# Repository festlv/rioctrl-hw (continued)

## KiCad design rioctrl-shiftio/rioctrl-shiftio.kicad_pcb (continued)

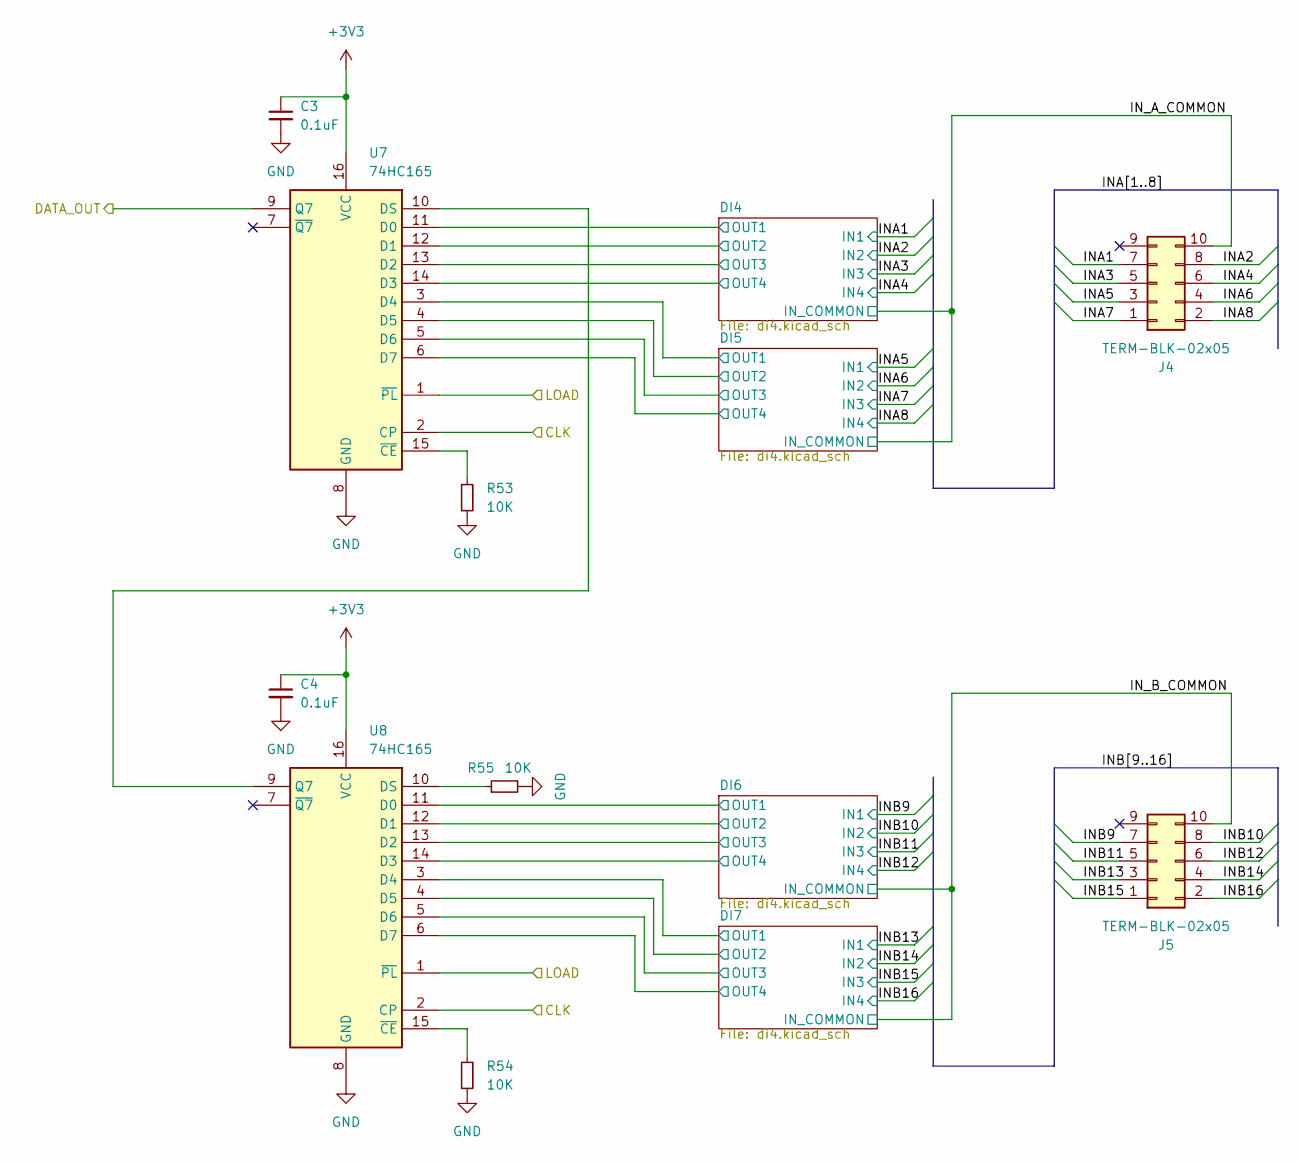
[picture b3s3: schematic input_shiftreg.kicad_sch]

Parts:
C3, C4: 0.1uF; C_0603_1608Metric; LCSC# C14663
J4, J5: TERM-BLK-02x05; JL15EDGRHC-35005B02; MPN JL15EDGRHC-35005B02; LCSC# C2908411
R53, R54, R55: 10K; R_0603_1608Metric; LCSC# C98220
U7, U8: 74HC165; SO-16_3.9x9.9mm_P1.27mm; MPN 74HC165D,653; LCSC# C5613

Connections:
+3V3: C3.1, C4.1, U7.16 (VCC), U8.16 (VCC); also elsewhere on the board
/Input shiftreg/CLK: U7.2 (CP), U8.2 (CP); also elsewhere on the board
/Input shiftreg/DATA_OUT: U7.9 (Q7); also elsewhere on the board
/Input shiftreg/DI4/OUT1: U7.11 (D0); also elsewhere on the board
/Input shiftreg/DI4/OUT2: U7.12 (D1); also elsewhere on the board
/Input shiftreg/DI4/OUT3: U7.13 (D2); also elsewhere on the board
/Input shiftreg/DI4/OUT4: U7.14 (D3); also elsewhere on the board
/Input shiftreg/DI5/OUT1: U7.3 (D4); also elsewhere on the board
/Input shiftreg/DI5/OUT2: U7.4 (D5); also elsewhere on the board
/Input shiftreg/DI5/OUT3: U7.5 (D6); also elsewhere on the board
/Input shiftreg/DI5/OUT4: U7.6 (D7); also elsewhere on the board
/Input shiftreg/DI6/OUT1: U8.11 (D0); also elsewhere on the board
/Input shiftreg/DI6/OUT2: U8.12 (D1); also elsewhere on the board
/Input shiftreg/DI6/OUT3: U8.13 (D2); also elsewhere on the board
/Input shiftreg/DI6/OUT4: U8.14 (D3); also elsewhere on the board
/Input shiftreg/DI7/OUT1: U8.3 (D4); also elsewhere on the board
/Input shiftreg/DI7/OUT2: U8.4 (D5); also elsewhere on the board
/Input shiftreg/DI7/OUT3: U8.5 (D6); also elsewhere on the board
/Input shiftreg/DI7/OUT4: U8.6 (D7); also elsewhere on the board
/Input shiftreg/INA1: J4.7; also elsewhere on the board
/Input shiftreg/INA2: J4.8; also elsewhere on the board
/Input shiftreg/INA3: J4.5; also elsewhere on the board
/Input shiftreg/INA4: J4.6; also elsewhere on the board
/Input shiftreg/INA5: J4.3; also elsewhere on the board
/Input shiftreg/INA6: J4.4; also elsewhere on the board
/Input shiftreg/INA7: J4.1; also elsewhere on the board
/Input shiftreg/INA8: J4.2; also elsewhere on the board
/Input shiftreg/INB9: J5.7; also elsewhere on the board
/Input shiftreg/INB10: J5.8; also elsewhere on the board
/Input shiftreg/INB11: J5.5; also elsewhere on the board
/Input shiftreg/INB12: J5.6; also elsewhere on the board
/Input shiftreg/INB13: J5.3; also elsewhere on the board
/Input shiftreg/INB14: J5.4; also elsewhere on the board
/Input shiftreg/INB15: J5.1; also elsewhere on the board
/Input shiftreg/INB16: J5.2; also elsewhere on the board
/Input shiftreg/IN_A_COMMON: J4.10; also elsewhere on the board
/Input shiftreg/IN_B_COMMON: J5.10; also elsewhere on the board
/Input shiftreg/LOAD: U7.1 (~PL), U8.1 (~PL); also elsewhere on the board
GND: C3.2, C4.2, R53.2, R54.2, R55.2, U7.8 (GND), U8.8 (GND); also elsewhere on the board
unnamed: U7.10 (DS), U8.9 (Q7)
unnamed: R53.1, U7.15 (~CE)
unnamed: R55.1, U8.10 (DS)
unnamed: R54.1, U8.15 (~CE)

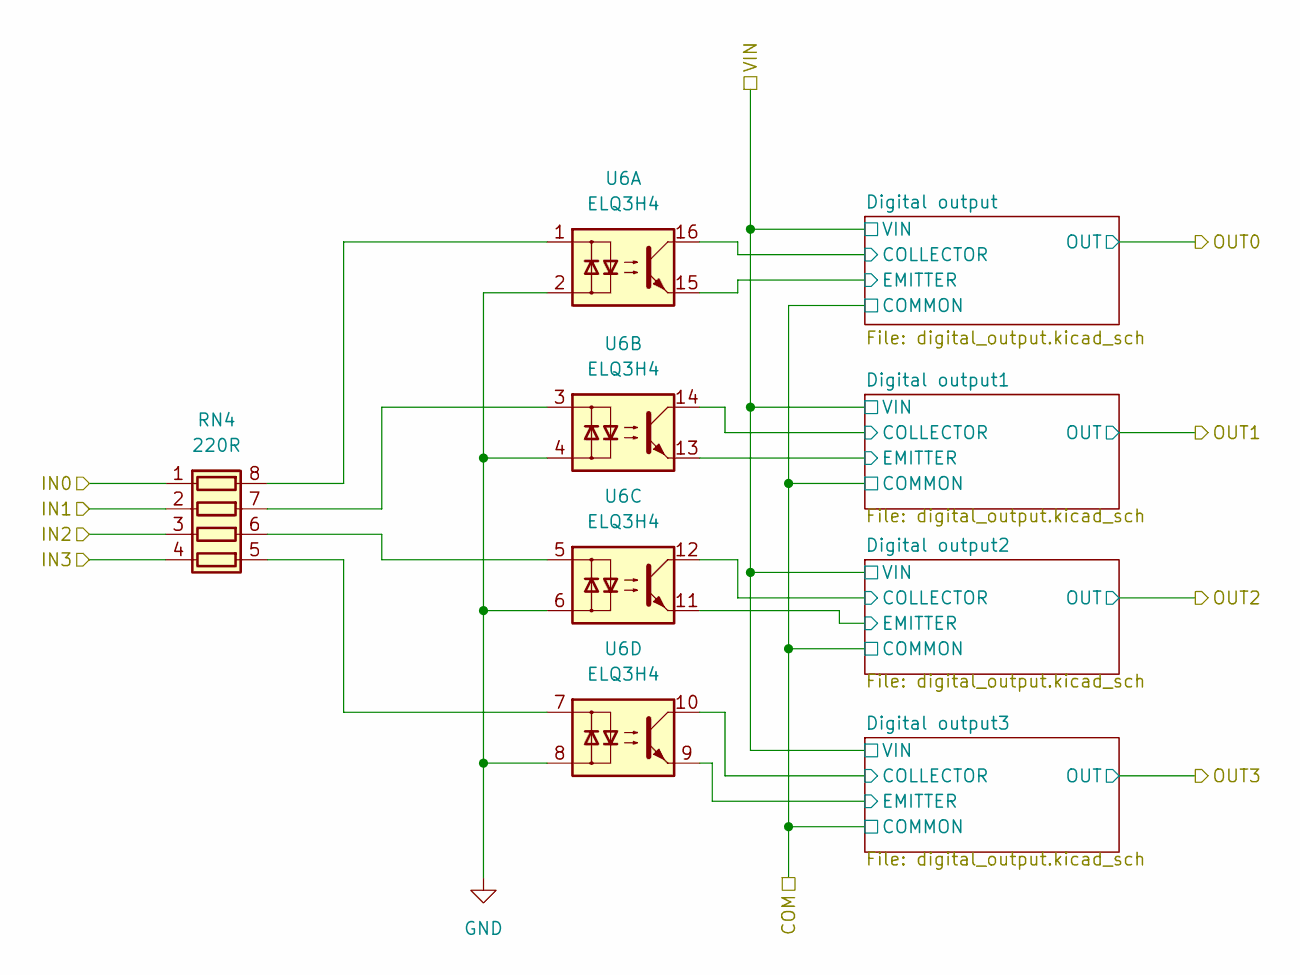
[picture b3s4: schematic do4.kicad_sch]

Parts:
RN4: 220R; R_Array_Convex_4x0603; LCSC# C706474
U6: ELQ3H4; SOIC-16W_5.3x10.2mm_P1.27mm; MPN ELQ3H4(TA)-G; LCSC# C150957

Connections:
/Output shiftreg/DOB2/Digital output1/COLLECTOR: U6.14; also elsewhere on the board
/Output shiftreg/DOB2/Digital output1/EMITTER: U6.13; also elsewhere on the board
/Output shiftreg/DOB2/Digital output2/COLLECTOR: U6.12; also elsewhere on the board
/Output shiftreg/DOB2/Digital output2/EMITTER: U6.11; also elsewhere on the board
/Output shiftreg/DOB2/Digital output3/COLLECTOR: U6.10; also elsewhere on the board
/Output shiftreg/DOB2/Digital output3/EMITTER: U6.9; also elsewhere on the board
/Output shiftreg/DOB2/Digital output/COLLECTOR: U6.16; also elsewhere on the board
/Output shiftreg/DOB2/Digital output/EMITTER: U6.15; also elsewhere on the board
/Output shiftreg/DOB2/IN0: RN4.1 (R1.1); also elsewhere on the board
/Output shiftreg/DOB2/IN1: RN4.2 (R2.1); also elsewhere on the board
/Output shiftreg/DOB2/IN2: RN4.3 (R3.1); also elsewhere on the board
/Output shiftreg/DOB2/IN3: RN4.4 (R4.1); also elsewhere on the board
GND: U6.2, U6.4, U6.6, U6.8; also elsewhere on the board
unnamed: RN4.8 (R1.2), U6.1
unnamed: RN4.7 (R2.2), U6.3
unnamed: RN4.6 (R3.2), U6.5
unnamed: RN4.5 (R4.2), U6.7

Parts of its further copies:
RN1, RN2, RN3: 220R; R_Array_Convex_4x0603; LCSC# C706474
U3, U4, U5: ELQ3H4; SOIC-16W_5.3x10.2mm_P1.27mm; MPN ELQ3H4(TA)-G; LCSC# C150957

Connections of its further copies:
/Output shiftreg/DOA1/Digital output1/COLLECTOR: U3.14; also elsewhere on the board
/Output shiftreg/DOA1/Digital output1/EMITTER: U3.13; also elsewhere on the board
/Output shiftreg/DOA1/Digital output2/COLLECTOR: U3.12; also elsewhere on the board
/Output shiftreg/DOA1/Digital output2/EMITTER: U3.11; also elsewhere on the board
/Output shiftreg/DOA1/Digital output3/COLLECTOR: U3.10; also elsewhere on the board
/Output shiftreg/DOA1/Digital output3/EMITTER: U3.9; also elsewhere on the board
/Output shiftreg/DOA1/Digital output/COLLECTOR: U3.16; also elsewhere on the board
/Output shiftreg/DOA1/Digital output/EMITTER: U3.15; also elsewhere on the board
/Output shiftreg/DOA1/IN0: RN1.1 (R1.1); also elsewhere on the board
/Output shiftreg/DOA1/IN1: RN1.2 (R2.1); also elsewhere on the board
/Output shiftreg/DOA1/IN2: RN1.3 (R3.1); also elsewhere on the board
/Output shiftreg/DOA1/IN3: RN1.4 (R4.1); also elsewhere on the board
/Output shiftreg/DOA2/Digital output1/COLLECTOR: U4.14; also elsewhere on the board
/Output shiftreg/DOA2/Digital output1/EMITTER: U4.13; also elsewhere on the board
/Output shiftreg/DOA2/Digital output2/COLLECTOR: U4.12; also elsewhere on the board
/Output shiftreg/DOA2/Digital output2/EMITTER: U4.11; also elsewhere on the board
/Output shiftreg/DOA2/Digital output3/COLLECTOR: U4.10; also elsewhere on the board
/Output shiftreg/DOA2/Digital output3/EMITTER: U4.9; also elsewhere on the board
/Output shiftreg/DOA2/Digital output/COLLECTOR: U4.16; also elsewhere on the board
/Output shiftreg/DOA2/Digital output/EMITTER: U4.15; also elsewhere on the board
/Output shiftreg/DOA2/IN0: RN2.1 (R1.1); also elsewhere on the board
/Output shiftreg/DOA2/IN1: RN2.2 (R2.1); also elsewhere on the board
/Output shiftreg/DOA2/IN2: RN2.3 (R3.1); also elsewhere on the board
/Output shiftreg/DOA2/IN3: RN2.4 (R4.1); also elsewhere on the board
/Output shiftreg/DOB1/Digital output1/COLLECTOR: U5.14; also elsewhere on the board
/Output shiftreg/DOB1/Digital output1/EMITTER: U5.13; also elsewhere on the board
/Output shiftreg/DOB1/Digital output2/COLLECTOR: U5.12; also elsewhere on the board
/Output shiftreg/DOB1/Digital output2/EMITTER: U5.11; also elsewhere on the board
/Output shiftreg/DOB1/Digital output3/COLLECTOR: U5.10; also elsewhere on the board
/Output shiftreg/DOB1/Digital output3/EMITTER: U5.9; also elsewhere on the board
/Output shiftreg/DOB1/Digital output/COLLECTOR: U5.16; also elsewhere on the board
/Output shiftreg/DOB1/Digital output/EMITTER: U5.15; also elsewhere on the board
/Output shiftreg/DOB1/IN0: RN3.1 (R1.1); also elsewhere on the board
/Output shiftreg/DOB1/IN1: RN3.2 (R2.1); also elsewhere on the board
/Output shiftreg/DOB1/IN2: RN3.3 (R3.1); also elsewhere on the board
/Output shiftreg/DOB1/IN3: RN3.4 (R4.1); also elsewhere on the board
GND: U3.2, U3.4, U3.6, U3.8, U4.2, U4.4, U4.6, U4.8, U5.2, U5.4, U5.6, U5.8; also elsewhere on the board
unnamed: RN1.8 (R1.2), U3.1
unnamed: RN1.7 (R2.2), U3.3
unnamed: RN1.6 (R3.2), U3.5
unnamed: RN1.5 (R4.2), U3.7
unnamed: RN2.8 (R1.2), U4.1
unnamed: RN2.7 (R2.2), U4.3
unnamed: RN2.6 (R3.2), U4.5
unnamed: RN2.5 (R4.2), U4.7
unnamed: RN3.8 (R1.2), U5.1
unnamed: RN3.7 (R2.2), U5.3
unnamed: RN3.6 (R3.2), U5.5
unnamed: RN3.5 (R4.2), U5.7

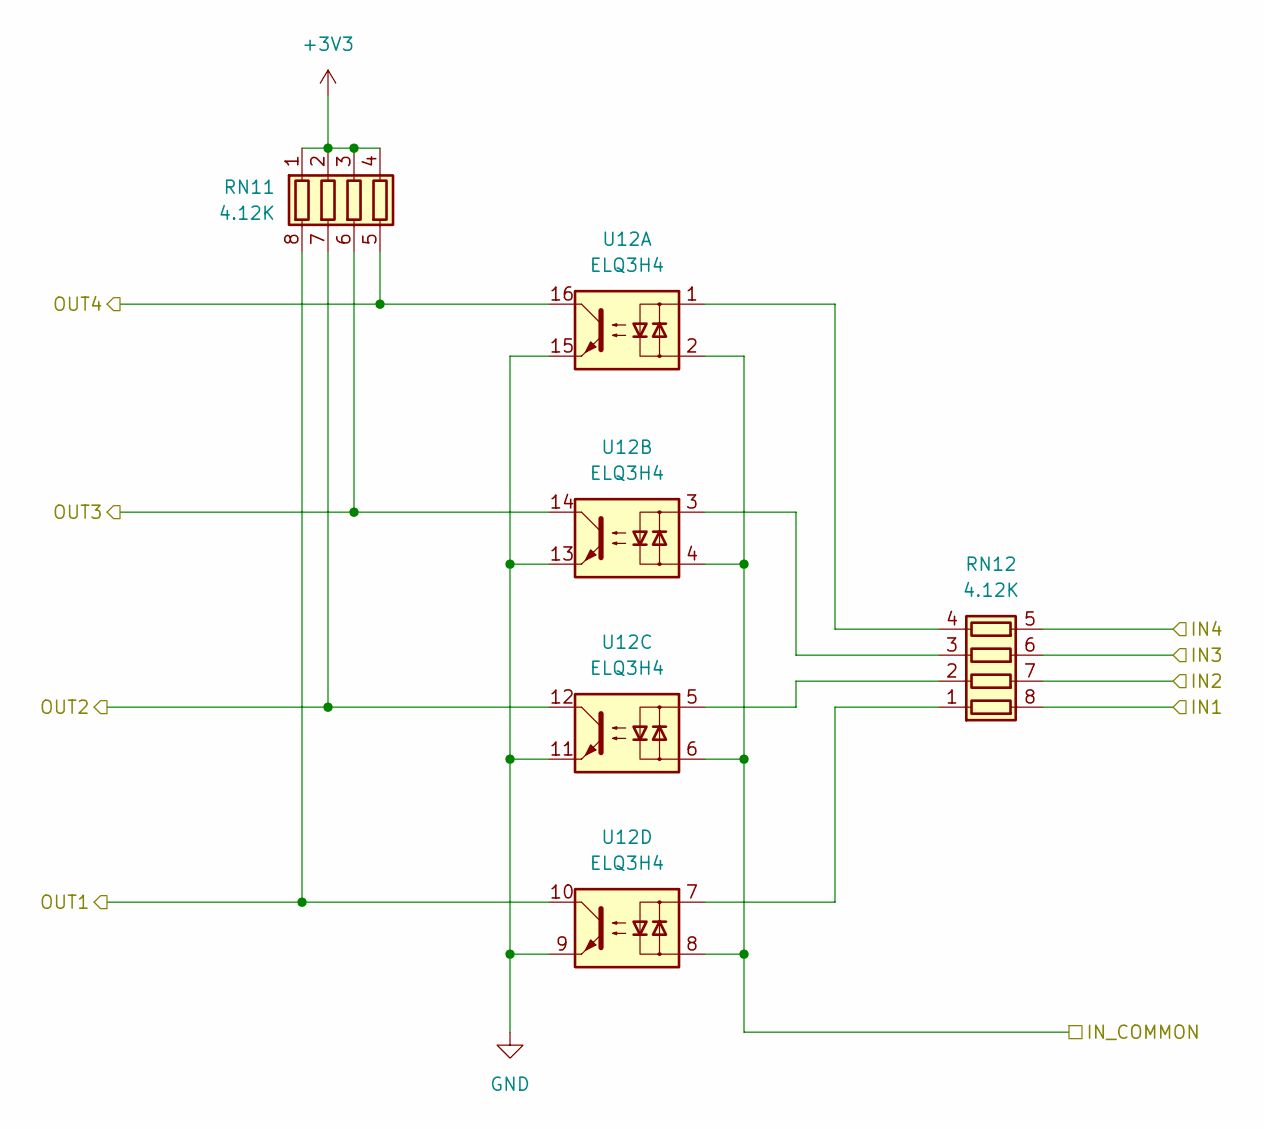
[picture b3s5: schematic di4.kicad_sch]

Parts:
RN11, RN12: 4.12K; R_Array_Convex_4x0603; LCSC# C728970
U12: ELQ3H4; SOIC-16W_5.3x10.2mm_P1.27mm; MPN ELQ3H4(TA)-G; LCSC# C150957

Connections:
+3V3: RN11.1 (R1.1), RN11.2 (R2.1), RN11.3 (R3.1), RN11.4 (R4.1); also elsewhere on the board
/Input shiftreg/DI7/OUT1: RN11.8 (R1.2), U12.10; also elsewhere on the board
/Input shiftreg/DI7/OUT2: RN11.7 (R2.2), U12.12; also elsewhere on the board
/Input shiftreg/DI7/OUT3: RN11.6 (R3.2), U12.14; also elsewhere on the board
/Input shiftreg/DI7/OUT4: RN11.5 (R4.2), U12.16; also elsewhere on the board
/Input shiftreg/INB13: RN12.8 (R1.2); also elsewhere on the board
/Input shiftreg/INB14: RN12.7 (R2.2); also elsewhere on the board
/Input shiftreg/INB15: RN12.6 (R3.2); also elsewhere on the board
/Input shiftreg/INB16: RN12.5 (R4.2); also elsewhere on the board
/Input shiftreg/IN_B_COMMON: U12.2, U12.4, U12.6, U12.8; also elsewhere on the board
GND: U12.9, U12.11, U12.13, U12.15; also elsewhere on the board
unnamed: RN12.1 (R1.1), U12.7
unnamed: RN12.2 (R2.1), U12.5
unnamed: RN12.3 (R3.1), U12.3
unnamed: RN12.4 (R4.1), U12.1

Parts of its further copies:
RN5, RN6, RN7, RN8, RN9, RN10: 4.12K; R_Array_Convex_4x0603; LCSC# C728970
U9, U10, U11: ELQ3H4; SOIC-16W_5.3x10.2mm_P1.27mm; MPN ELQ3H4(TA)-G; LCSC# C150957

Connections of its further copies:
+3V3: RN5.1 (R1.1), RN5.2 (R2.1), RN5.3 (R3.1), RN5.4 (R4.1), RN7.1 (R1.1), RN7.2 (R2.1), RN7.3 (R3.1), RN7.4 (R4.1), RN9.1 (R1.1), RN9.2 (R2.1), RN9.3 (R3.1), RN9.4 (R4.1); also elsewhere on the board
/Input shiftreg/DI4/OUT1: RN5.8 (R1.2), U9.10; also elsewhere on the board
/Input shiftreg/DI4/OUT2: RN5.7 (R2.2), U9.12; also elsewhere on the board
/Input shiftreg/DI4/OUT3: RN5.6 (R3.2), U9.14; also elsewhere on the board
/Input shiftreg/DI4/OUT4: RN5.5 (R4.2), U9.16; also elsewhere on the board
/Input shiftreg/DI5/OUT1: RN7.8 (R1.2), U10.10; also elsewhere on the board
/Input shiftreg/DI5/OUT2: RN7.7 (R2.2), U10.12; also elsewhere on the board
/Input shiftreg/DI5/OUT3: RN7.6 (R3.2), U10.14; also elsewhere on the board
/Input shiftreg/DI5/OUT4: RN7.5 (R4.2), U10.16; also elsewhere on the board
/Input shiftreg/DI6/OUT1: RN9.8 (R1.2), U11.10; also elsewhere on the board
/Input shiftreg/DI6/OUT2: RN9.7 (R2.2), U11.12; also elsewhere on the board
/Input shiftreg/DI6/OUT3: RN9.6 (R3.2), U11.14; also elsewhere on the board
/Input shiftreg/DI6/OUT4: RN9.5 (R4.2), U11.16; also elsewhere on the board
/Input shiftreg/INA1: RN6.8 (R1.2); also elsewhere on the board
/Input shiftreg/INA2: RN6.7 (R2.2); also elsewhere on the board
/Input shiftreg/INA3: RN6.6 (R3.2); also elsewhere on the board
/Input shiftreg/INA4: RN6.5 (R4.2); also elsewhere on the board
/Input shiftreg/INA5: RN8.8 (R1.2); also elsewhere on the board
/Input shiftreg/INA6: RN8.7 (R2.2); also elsewhere on the board
/Input shiftreg/INA7: RN8.6 (R3.2); also elsewhere on the board
/Input shiftreg/INA8: RN8.5 (R4.2); also elsewhere on the board
/Input shiftreg/INB9: RN10.8 (R1.2); also elsewhere on the board
/Input shiftreg/INB10: RN10.7 (R2.2); also elsewhere on the board
/Input shiftreg/INB11: RN10.6 (R3.2); also elsewhere on the board
/Input shiftreg/INB12: RN10.5 (R4.2); also elsewhere on the board
/Input shiftreg/IN_A_COMMON: U9.2, U9.4, U9.6, U9.8, U10.2, U10.4, U10.6, U10.8; also elsewhere on the board
/Input shiftreg/IN_B_COMMON: U11.2, U11.4, U11.6, U11.8; also elsewhere on the board
GND: U9.9, U9.11, U9.13, U9.15, U10.9, U10.11, U10.13, U10.15, U11.9, U11.11, U11.13, U11.15; also elsewhere on the board
unnamed: RN6.1 (R1.1), U9.7
unnamed: RN6.2 (R2.1), U9.5
unnamed: RN6.3 (R3.1), U9.3
unnamed: RN6.4 (R4.1), U9.1
unnamed: RN8.1 (R1.1), U10.7
unnamed: RN8.2 (R2.1), U10.5
unnamed: RN8.3 (R3.1), U10.3
unnamed: RN8.4 (R4.1), U10.1
unnamed: RN10.1 (R1.1), U11.7
unnamed: RN10.2 (R2.1), U11.5
unnamed: RN10.3 (R3.1), U11.3
unnamed: RN10.4 (R4.1), U11.1

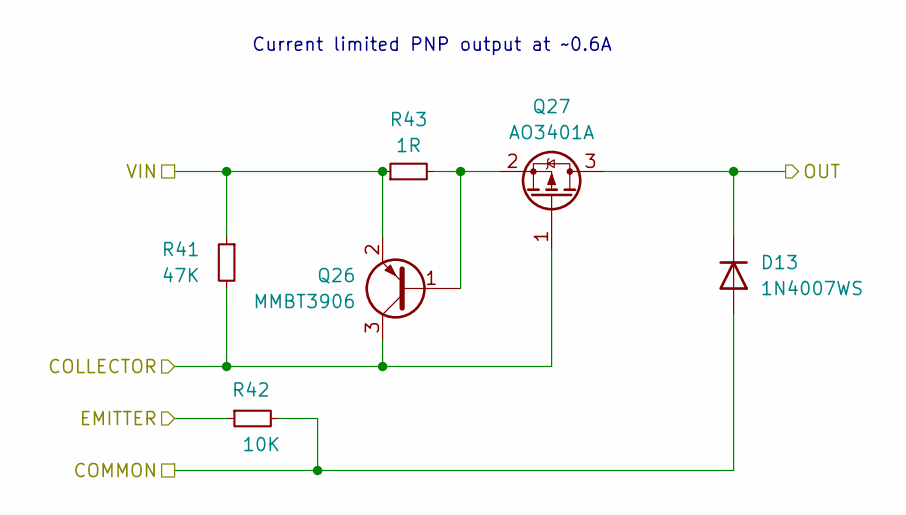
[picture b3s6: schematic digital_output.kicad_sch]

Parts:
D13: 1N4007WS; D_SOD-323F; MPN 1N4007WS; LCSC# C7528872
Q26: MMBT3906; SOT-23; MPN MMBT3906; LCSC# C727128
Q27: AO3401A; SOT-23; MPN AO3401A; LCSC# C347476
R41: 47K; R_0603_1608Metric; LCSC# C105579
R42: 10K; R_0603_1608Metric; LCSC# C98220
R43: 1R; R_0805_2012Metric; LCSC# C131397

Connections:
/Output shiftreg/DO14: D13.1 (K), Q27.3 (D); also elsewhere on the board
/Output shiftreg/DOB2/Digital output1/COLLECTOR: Q26.3 (C), Q27.1 (G), R41.2; also elsewhere on the board
/Output shiftreg/DOB2/Digital output1/EMITTER: R42.1; also elsewhere on the board
/Output shiftreg/DOB_GND: D13.2 (A), R42.2; also elsewhere on the board
/Output shiftreg/DOB_VIN: Q26.2 (E), R41.1, R43.1; also elsewhere on the board
unnamed: Q26.1 (B), Q27.2 (S), R43.2

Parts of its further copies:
D1, D2, D3, D4, D5, D6, D7, D8, D9, D10, D11, D12, D14, D15, D16: 1N4007WS; D_SOD-323F; MPN 1N4007WS; LCSC# C7528872
Q2, Q4, Q6, Q8, Q10, Q12, Q14, Q16, Q18, Q20, Q22, Q24, Q28, Q30, Q32: MMBT3906; SOT-23; MPN MMBT3906; LCSC# C727128
Q3, Q5, Q7, Q9, Q11, Q13, Q15, Q17, Q19, Q21, Q23, Q25, Q29, Q31, Q33: AO3401A; SOT-23; MPN AO3401A; LCSC# C347476
R5, R8, R11, R14, R17, R20, R23, R26, R29, R32, R35, R38, R44, R47, R50: 47K; R_0603_1608Metric; LCSC# C105579
R6, R9, R12, R15, R18, R21, R24, R27, R30, R33, R36, R39, R45, R48, R51: 10K; R_0603_1608Metric; LCSC# C98220
R7, R10, R13, R16, R19, R22, R25, R28, R31, R34, R37, R40, R46, R49, R52: 1R; R_0805_2012Metric; LCSC# C131397

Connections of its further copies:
/Output shiftreg/DO1: D1.1 (K), Q3.3 (D); also elsewhere on the board
/Output shiftreg/DO2: D2.1 (K), Q5.3 (D); also elsewhere on the board
/Output shiftreg/DO3: D3.1 (K), Q7.3 (D); also elsewhere on the board
/Output shiftreg/DO4: D4.1 (K), Q9.3 (D); also elsewhere on the board
/Output shiftreg/DO5: D7.1 (K), Q15.3 (D); also elsewhere on the board
/Output shiftreg/DO6: D8.1 (K), Q17.3 (D); also elsewhere on the board
/Output shiftreg/DO7: D5.1 (K), Q11.3 (D); also elsewhere on the board
/Output shiftreg/DO8: D6.1 (K), Q13.3 (D); also elsewhere on the board
/Output shiftreg/DO9: D12.1 (K), Q25.3 (D); also elsewhere on the board
/Output shiftreg/DO10: D9.1 (K), Q19.3 (D); also elsewhere on the board
/Output shiftreg/DO11: D11.1 (K), Q23.3 (D); also elsewhere on the board
/Output shiftreg/DO12: D10.1 (K), Q21.3 (D); also elsewhere on the board
/Output shiftreg/DO13: D16.1 (K), Q33.3 (D); also elsewhere on the board
/Output shiftreg/DO15: D15.1 (K), Q31.3 (D); also elsewhere on the board
/Output shiftreg/DO16: D14.1 (K), Q29.3 (D); also elsewhere on the board
/Output shiftreg/DOA1/Digital output1/COLLECTOR: Q4.3 (C), Q5.1 (G), R8.2; also elsewhere on the board
/Output shiftreg/DOA1/Digital output1/EMITTER: R9.1; also elsewhere on the board
/Output shiftreg/DOA1/Digital output2/COLLECTOR: Q6.3 (C), Q7.1 (G), R11.2; also elsewhere on the board
/Output shiftreg/DOA1/Digital output2/EMITTER: R12.1; also elsewhere on the board
/Output shiftreg/DOA1/Digital output3/COLLECTOR: Q8.3 (C), Q9.1 (G), R14.2; also elsewhere on the board
/Output shiftreg/DOA1/Digital output3/EMITTER: R15.1; also elsewhere on the board
/Output shiftreg/DOA1/Digital output/COLLECTOR: Q2.3 (C), Q3.1 (G), R5.2; also elsewhere on the board
/Output shiftreg/DOA1/Digital output/EMITTER: R6.1; also elsewhere on the board
/Output shiftreg/DOA2/Digital output1/COLLECTOR: Q16.3 (C), Q17.1 (G), R26.2; also elsewhere on the board
/Output shiftreg/DOA2/Digital output1/EMITTER: R27.1; also elsewhere on the board
/Output shiftreg/DOA2/Digital output2/COLLECTOR: Q10.3 (C), Q11.1 (G), R17.2; also elsewhere on the board
/Output shiftreg/DOA2/Digital output2/EMITTER: R18.1; also elsewhere on the board
/Output shiftreg/DOA2/Digital output3/COLLECTOR: Q12.3 (C), Q13.1 (G), R20.2; also elsewhere on the board
/Output shiftreg/DOA2/Digital output3/EMITTER: R21.1; also elsewhere on the board
/Output shiftreg/DOA2/Digital output/COLLECTOR: Q14.3 (C), Q15.1 (G), R23.2; also elsewhere on the board
/Output shiftreg/DOA2/Digital output/EMITTER: R24.1; also elsewhere on the board
/Output shiftreg/DOA_GND: D1.2 (A), D2.2 (A), D3.2 (A), D4.2 (A), D5.2 (A), D6.2 (A), D7.2 (A), D8.2 (A), R6.2, R9.2, R12.2, R15.2, R18.2, R21.2, R24.2, R27.2; also elsewhere on the board
/Output shiftreg/DOA_VIN: Q2.2 (E), Q4.2 (E), Q6.2 (E), Q8.2 (E), Q10.2 (E), Q12.2 (E), Q14.2 (E), Q16.2 (E), R5.1, R7.1, R8.1, R10.1, R11.1, R13.1, R14.1, R16.1, R17.1, R19.1, R20.1, R22.1, R23.1, R25.1, R26.1, R28.1; also elsewhere on the board
/Output shiftreg/DOB1/Digital output1/COLLECTOR: Q18.3 (C), Q19.1 (G), R29.2; also elsewhere on the board
/Output shiftreg/DOB1/Digital output1/EMITTER: R30.1; also elsewhere on the board
/Output shiftreg/DOB1/Digital output2/COLLECTOR: Q22.3 (C), Q23.1 (G), R35.2; also elsewhere on the board
/Output shiftreg/DOB1/Digital output2/EMITTER: R36.1; also elsewhere on the board
/Output shiftreg/DOB1/Digital output3/COLLECTOR: Q20.3 (C), Q21.1 (G), R32.2; also elsewhere on the board
/Output shiftreg/DOB1/Digital output3/EMITTER: R33.1; also elsewhere on the board
/Output shiftreg/DOB1/Digital output/COLLECTOR: Q24.3 (C), Q25.1 (G), R38.2; also elsewhere on the board
/Output shiftreg/DOB1/Digital output/EMITTER: R39.1; also elsewhere on the board
/Output shiftreg/DOB2/Digital output2/COLLECTOR: Q30.3 (C), Q31.1 (G), R47.2; also elsewhere on the board
/Output shiftreg/DOB2/Digital output2/EMITTER: R48.1; also elsewhere on the board
/Output shiftreg/DOB2/Digital output3/COLLECTOR: Q28.3 (C), Q29.1 (G), R44.2; also elsewhere on the board
/Output shiftreg/DOB2/Digital output3/EMITTER: R45.1; also elsewhere on the board
/Output shiftreg/DOB2/Digital output/COLLECTOR: Q32.3 (C), Q33.1 (G), R50.2; also elsewhere on the board
/Output shiftreg/DOB2/Digital output/EMITTER: R51.1; also elsewhere on the board
/Output shiftreg/DOB_GND: D9.2 (A), D10.2 (A), D11.2 (A), D12.2 (A), D14.2 (A), D15.2 (A), D16.2 (A), R30.2, R33.2, R36.2, R39.2, R45.2, R48.2, R51.2; also elsewhere on the board
/Output shiftreg/DOB_VIN: Q18.2 (E), Q20.2 (E), Q22.2 (E), Q24.2 (E), Q28.2 (E), Q30.2 (E), Q32.2 (E), R29.1, R31.1, R32.1, R34.1, R35.1, R37.1, R38.1, R40.1, R44.1, R46.1, R47.1, R49.1, R50.1, R52.1; also elsewhere on the board
unnamed: Q2.1 (B), Q3.2 (S), R7.2
unnamed: Q4.1 (B), Q5.2 (S), R10.2
unnamed: Q6.1 (B), Q7.2 (S), R13.2
unnamed: Q8.1 (B), Q9.2 (S), R16.2
unnamed: Q10.1 (B), Q11.2 (S), R19.2
unnamed: Q12.1 (B), Q13.2 (S), R22.2
unnamed: Q14.1 (B), Q15.2 (S), R25.2
unnamed: Q16.1 (B), Q17.2 (S), R28.2
unnamed: Q18.1 (B), Q19.2 (S), R31.2
unnamed: Q20.1 (B), Q21.2 (S), R34.2
unnamed: Q22.1 (B), Q23.2 (S), R37.2
unnamed: Q24.1 (B), Q25.2 (S), R40.2
unnamed: Q28.1 (B), Q29.2 (S), R46.2
unnamed: Q30.1 (B), Q31.2 (S), R49.2
unnamed: Q32.1 (B), Q33.2 (S), R52.2

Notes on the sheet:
Current limited PNP output at ~0.6A

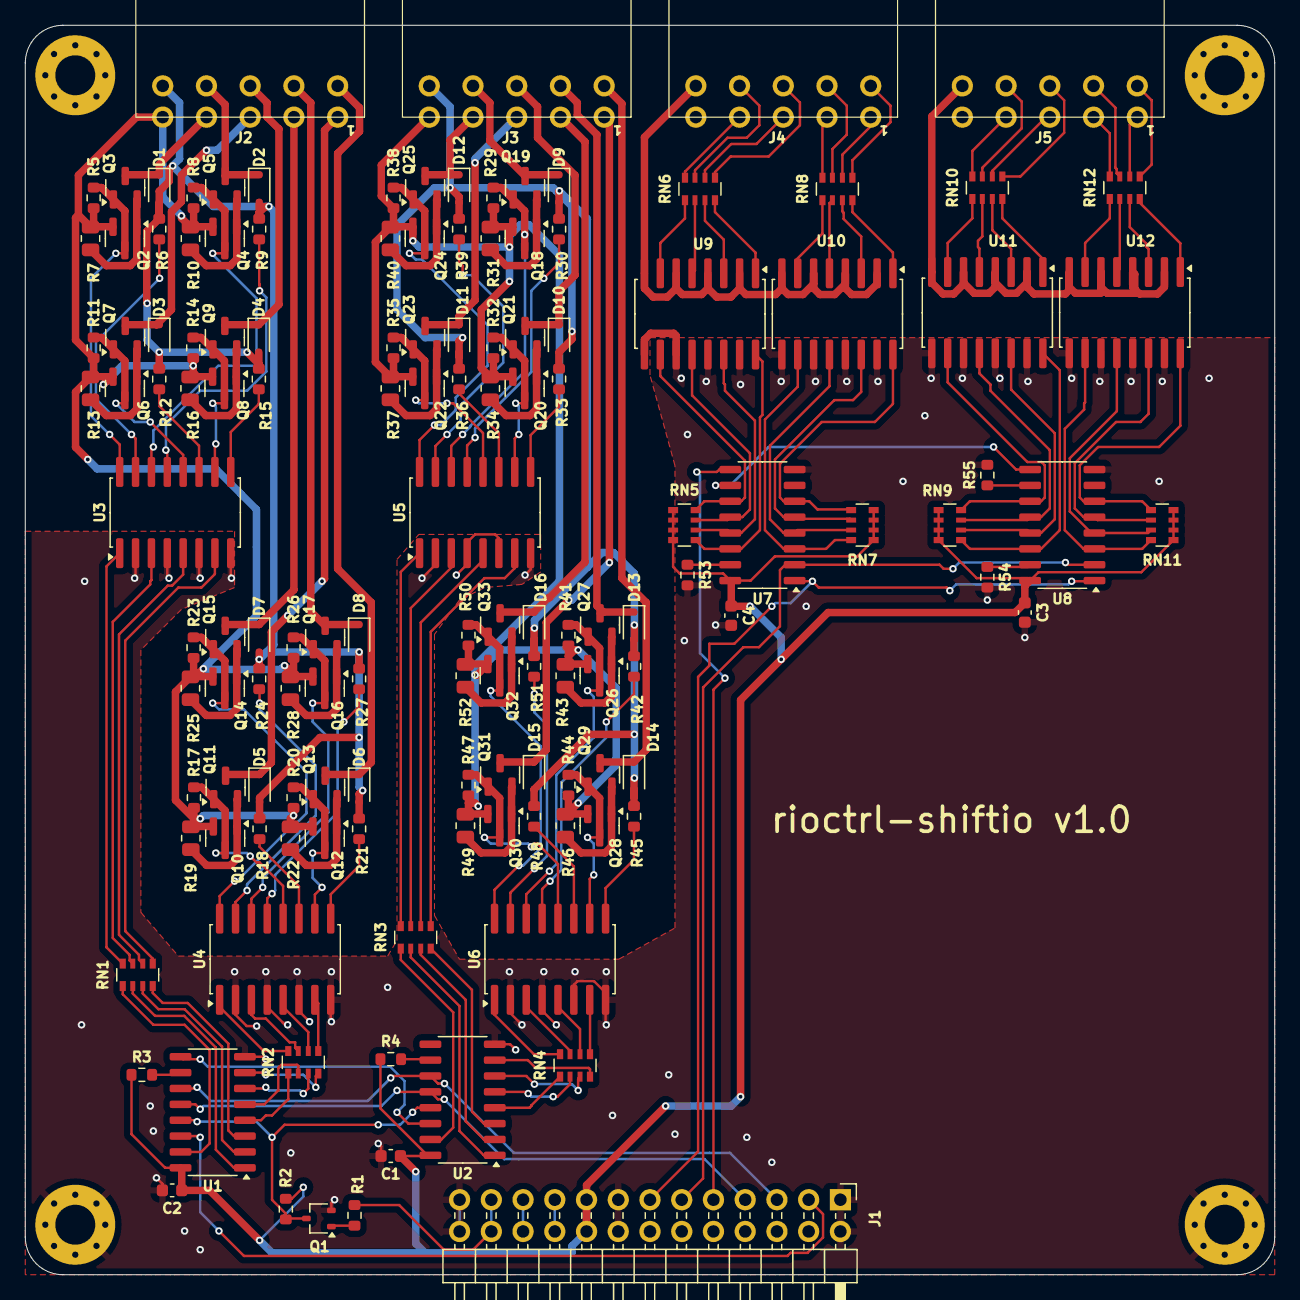
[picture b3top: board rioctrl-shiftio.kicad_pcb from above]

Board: 2 copper layers, 100.0 x 100.0 mm, 141 parts (0 on the bottom side), 170 nets.

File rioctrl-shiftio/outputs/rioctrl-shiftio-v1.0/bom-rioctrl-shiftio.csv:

"Refs","Value","Footprint","Manufacturer","MPN","Qty","DNP","LCSC#"
"C1-C4","0.1uF","Capacitor_SMD:C_0603_1608Metric","","","4","","C14663"
"D1-D16","1N4007WS","Diode_SMD:D_SOD-323F","MKSEMI","1N4007WS","16","","C7528872"
"J1","Conn_02x13_Odd_Even","Connector_PinHeader_2.54mm:PinHeader_2x13_P2.54mm_Horizontal","","","1","","C2894993"
"J2-J5","TERM-BLK-02x05","hadv-connectors:JL15EDGRHC-35005B02","JILN","JL15EDGRHC-35005B02","4","","C2908411"
"Q1","BSS138W","Package_TO_SOT_SMD:SOT-323_SC-70","Jiangsu Changjing Electronics Technology Co., Ltd.","BSS138W","1","","C504052"
"Q2,Q4,Q6,Q8,Q10,Q12,Q14,Q16,Q18,Q20,Q22,Q24,Q26,Q28,Q30,Q32","MMBT3906","Package_TO_SOT_SMD:SOT-23","TWGMC","MMBT3906","16","","C727128"
"Q3,Q5,Q7,Q9,Q11,Q13,Q15,Q17,Q19,Q21,Q23,Q25,Q27,Q29,Q31,Q33","AO3401A","Package_TO_SOT_SMD:SOT-23","UMW","AO3401A","16","","C347476"
"R1,R3,R4,R6,R9,R12,R15,R18,R21,R24,R27,R30,R33,R36,R39,R42,R45,R48,R51,R53-R55","10K","Resistor_SMD:R_0603_1608Metric","","","22","","C98220"
"R2","4K7","Resistor_SMD:R_0603_1608Metric","","","1","","C99782"
"R5,R8,R11,R14,R17,R20,R23,R26,R29,R32,R35,R38,R41,R44,R47,R50","47K","Resistor_SMD:R_0603_1608Metric","","","16","","C105579"
"R7,R10,R13,R16,R19,R22,R25,R28,R31,R34,R37,R40,R43,R46,R49,R52","1R","Resistor_SMD:R_0805_2012Metric","","","16","","C131397"
"RN1-RN4","220R","Resistor_SMD:R_Array_Convex_4x0603","","","4","","C706474"
"RN5-RN12","4.12K","Resistor_SMD:R_Array_Convex_4x0603","","","8","","C728970"
"U1,U2","74HC595","Package_SO:SO-16_3.9x9.9mm_P1.27mm","Nexperia","74HC595D,118","2","","C5947"
"U3-U6,U9-U12","ELQ3H4","Package_SO:SOIC-16W_5.3x10.2mm_P1.27mm","Everlight Elec","ELQ3H4(TA)-G","8","","C150957"
"U7,U8","74HC165","Package_SO:SO-16_3.9x9.9mm_P1.27mm","Nexperia","74HC165D,653","2","","C5613"
